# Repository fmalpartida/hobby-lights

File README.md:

# hobby-lights
Small light sequencer for hobby projects.

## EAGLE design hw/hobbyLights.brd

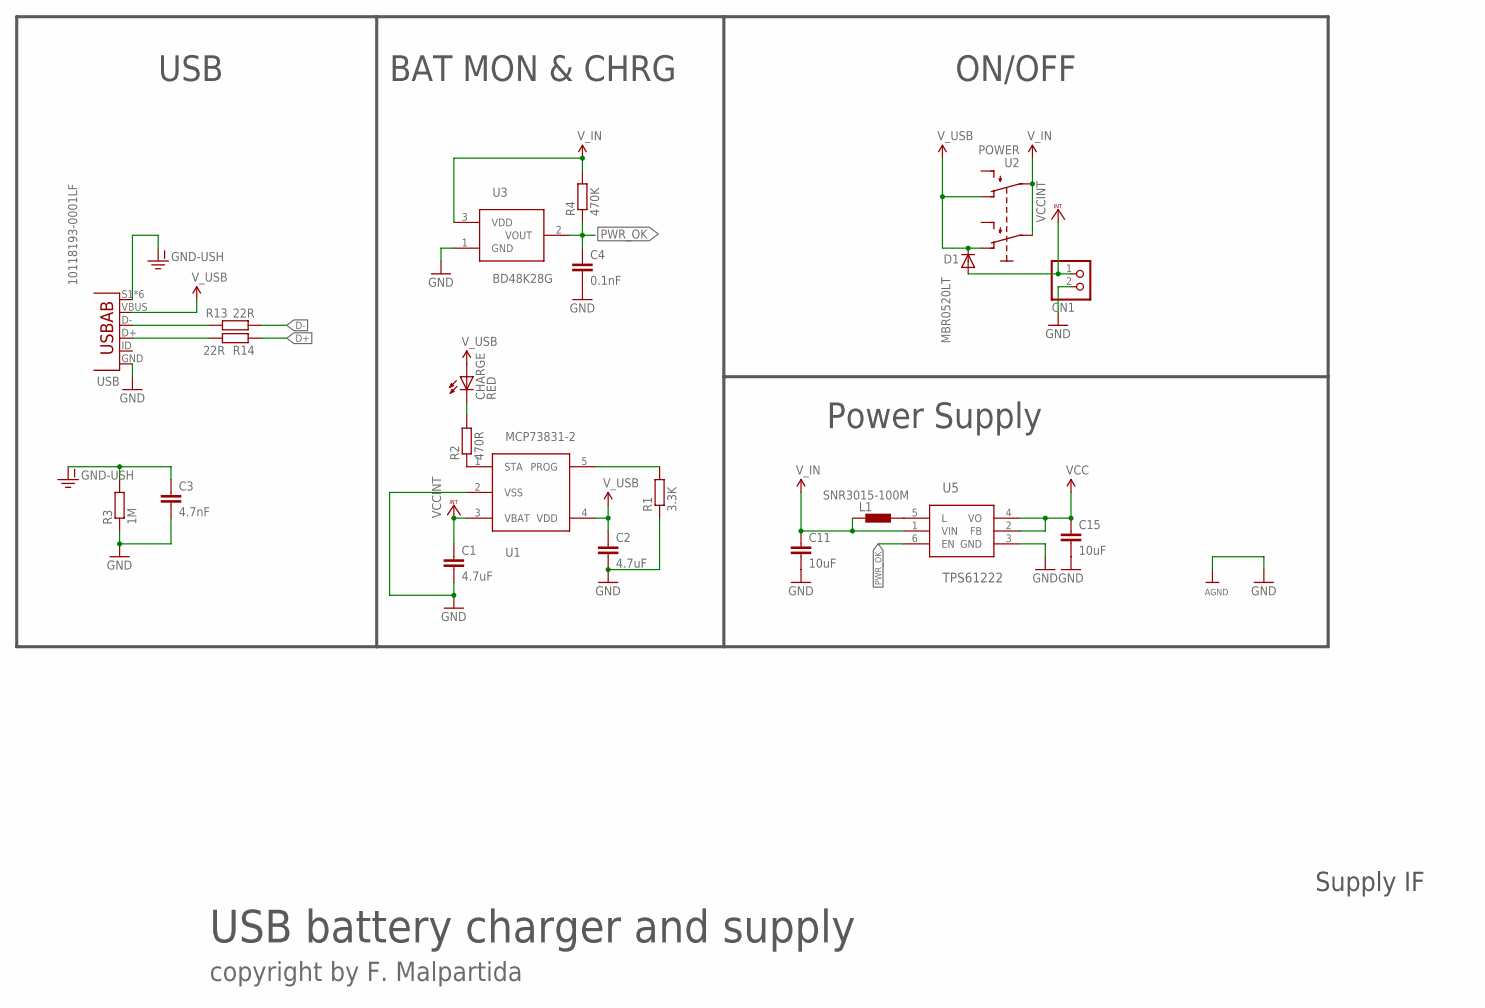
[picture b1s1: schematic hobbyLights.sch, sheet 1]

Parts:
C1, C2: 4.7uF; C0805
C3: 4.7nF; C0603
C4: 0.1nF; C0603
C11, C15: 10uF; C0805
CHARGE: RED; CHIPLED_0805
CN1: JST_2PIN-THM-RA; JST-PH-2-THM-RA
D1: MBR0520LT; SOD123
L1: SNR3015-100M; SRN3015
R1: 3.3K; R0603
R2: 470R; R0603
R3: 1M; R0603
R4: 470K; R0603
R13, R14: 22R; R0603
U1: MCP73831-2; SOT23-5
U2: POWER; SWITCH-JS202011
U3: BD48K28G; SSOP3
U5: TPS61222; DCK
USB: 10118193-0001LF; USB_MICRO_B

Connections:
D+: R14.1; also elsewhere on the board
D-: R13.1; also elsewhere on the board
GND: C1.2, C2.2, C3.2, C4.2, C11.2, C15.2, CN1.2 (1), R1.1, R3.1, U1.2 (VSS), U3.1 (GND), U5.3 (GND), USB.GND; also elsewhere on the board
GND-ISO: C3.1, R3.2, USB.S1 (SHIELD), USB.S2 (SHIELD), USB.S3 (SHIELD), USB.S4 (SHIELD), USB.S5 (SHIELD), USB.S6 (SHIELD)
unnamed: R1.2, U1.5 (PROG)
unnamed: R2.1, U1.1 (STA)
unnamed: CHARGE.C, R2.2
unnamed: R13.2, USB.D-
unnamed: R14.2, USB.D+
unnamed: L1.2, U5.5 (L)
PWR_OK: C4.1, R4.1, U3.2 (VOUT), U5.6 (EN)
VCC: C15.1, U5.2 (FB), U5.4 (VO); also elsewhere on the board
VCCINT: C1.1, CN1.1 (2), D1.A, U1.3 (VBAT)
V_BATT: C11.1, L1.1, R4.2, U2.P2, U2.P5 (P1), U3.3 (VDD), U5.1 (VIN); also elsewhere on the board
V_USB: C2.1, CHARGE.A, D1.C, U1.4 (VDD), U2.P1 (O), U2.P4 (O1), USB.VBUS

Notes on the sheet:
USB
BAT MON & CHRG
Power Supply
ON/OFF
USB battery charger and supply
Supply IF
copyright by F. Malpartida

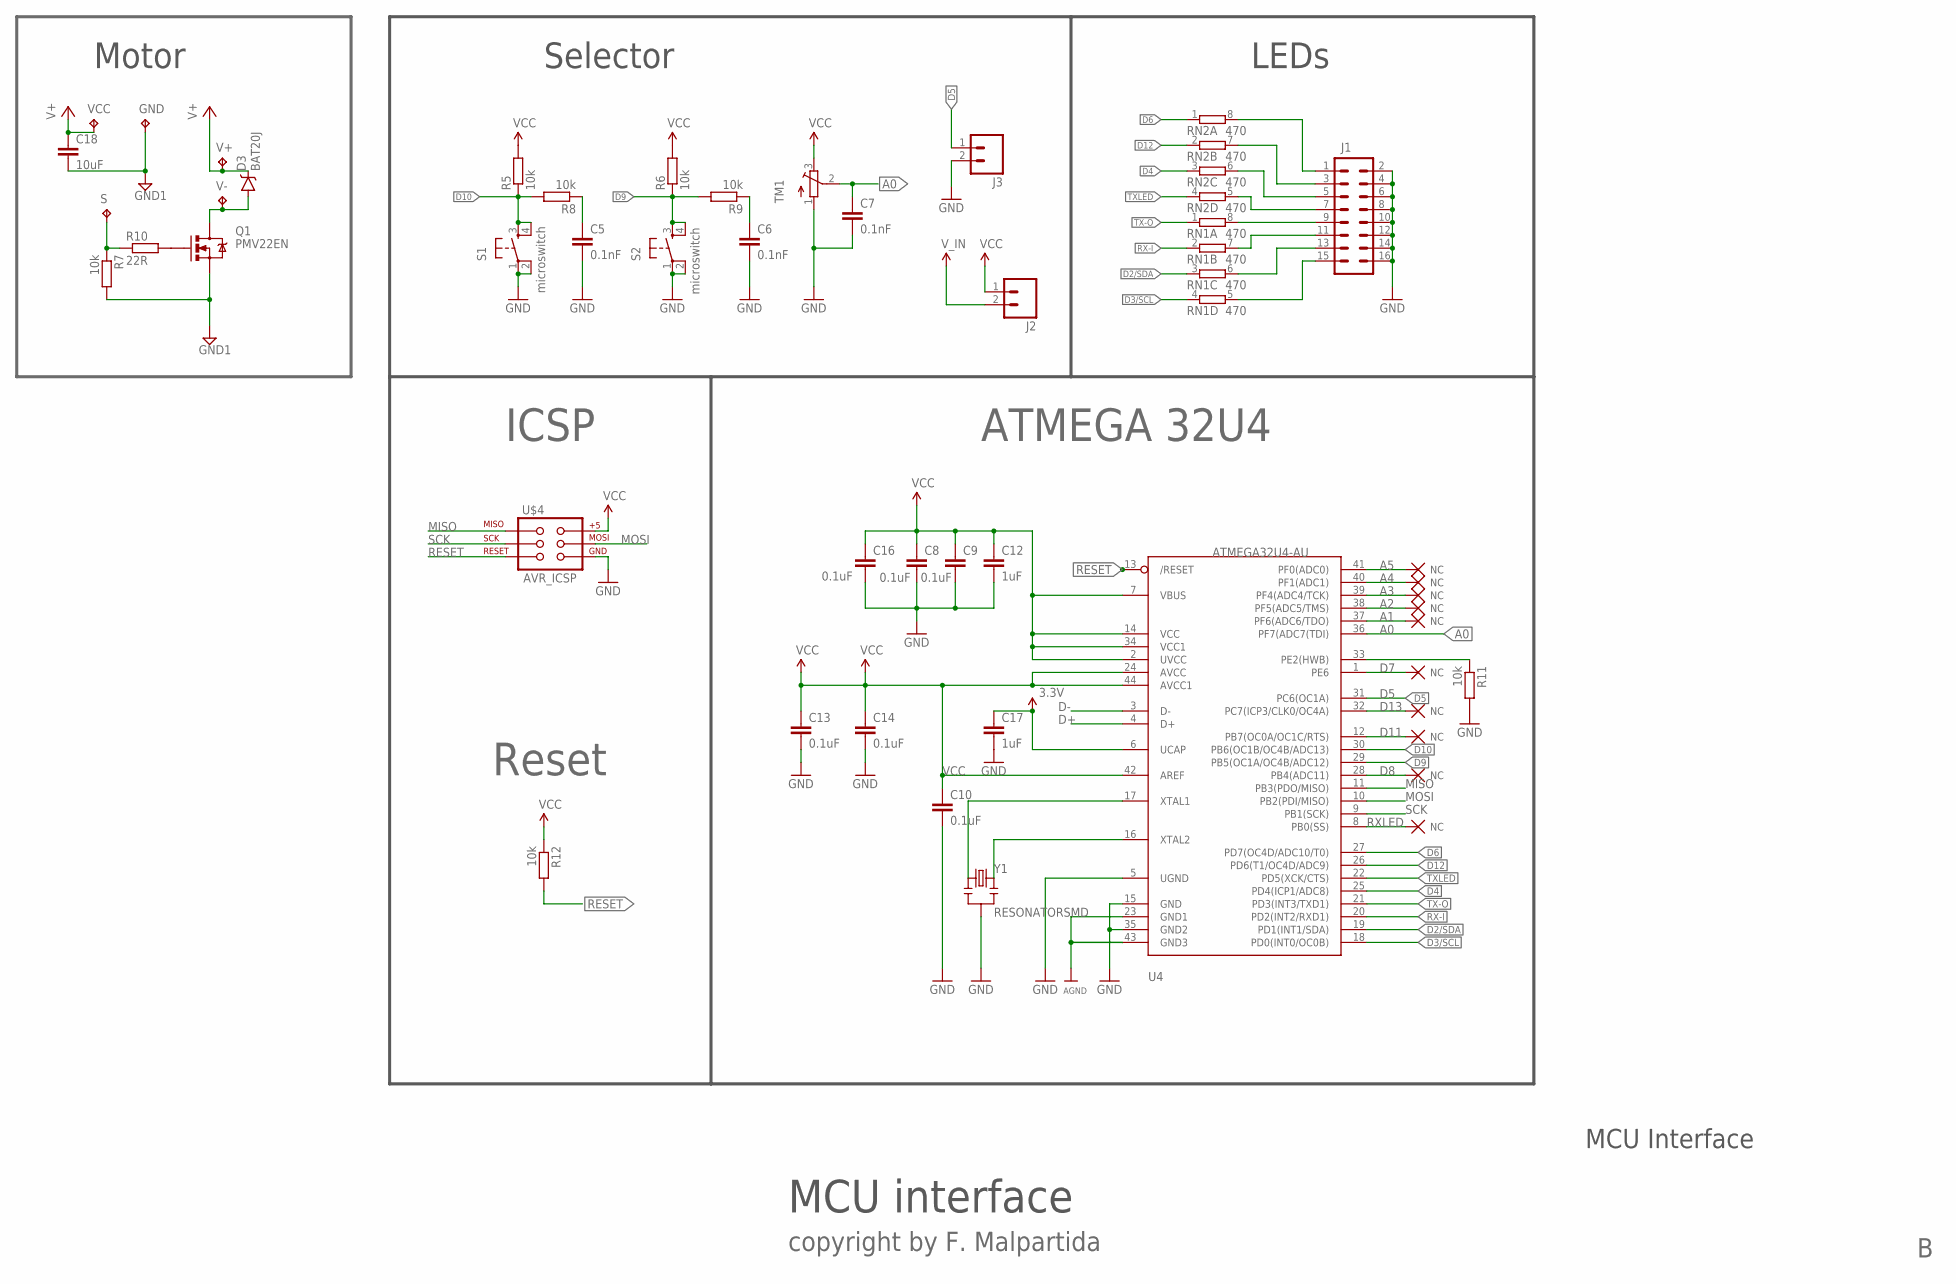
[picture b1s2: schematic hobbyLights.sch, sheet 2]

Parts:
C5, C6, C7: 0.1nF; C0603
C8, C9, C10, C13, C14, C16: 0.1uF; C0603
C12, C17: 1uF; C0603
C18: 10uF; C0805
D3: BAT20J; SOD-323
GND: TPTP20SQ; TP20SQ
J1: M08X2; 2X8
J2, J3: M02PTH; 1X02
Q1: PMV22EN; SOT23-3
R5, R6, R7, R8, R9, R11, R12: 10k; R0603
R10: 22R; R0603
RN1, RN2: 470; EXBS8V
S: TPTP20SQ; TP20SQ
S1, S2: microswitch; SPARKFUN_TACTILE_SWITCH_SMD
TM1: TRIMPOTTC33X; TC33X
U4: ATMEGA32U4-AU; ADAFRUIT_TQFP44
U$4: AVR_ICSP; ICSP_SMD
V+: TPTP20SQ; TP20SQ
V-: TPTP20SQ; TP20SQ
VCC: TPTP20SQ; TP20SQ
Y1: RESONATORSMD; RESONATOR-SMD

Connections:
3.3V: C17.1, U4.6 (UCAP)
A0: C7.1, TM1.2 (S), U4.36 (PF7(ADC7(TDI))
A1: U4.37 (PF6(ADC6/TDO))
A2: U4.38 (PF5(ADC5/TMS))
A3: U4.39 (PF4(ADC4/TCK))
A4: U4.40 (PF1(ADC1))
A5: U4.41 (PF0(ADC0))
D2/SDA: RN1.3 (1), U4.19 (PD1(INT1/SDA))
D3/SCL: RN1.4 (1), U4.18 (PD0(INT0/OC0B))
D4: RN2.3 (1), U4.25 (PD4(ICP1/ADC8))
D5: J3.1, U4.31 (PC6(OC1A))
D6: RN2.1, U4.27 (PD7(OC4D/ADC10/T0))
D7: U4.1 (PE6)
D8: U4.28 (PB4(ADC11))
D9: R6.1, R9.2, S2.3, S2.4, U4.29 (PB5(OC1A/OC4B/ADC12))
D10: R5.1, R8.2, S1.3, S1.4, U4.30 (PB6(OC1B/OC4B/ADC13))
D11: U4.12 (PB7(OC0A/OC1C/RTS))
D12: RN2.2 (1), U4.26 (PD6(T1/OC4D/ADC9))
D13: U4.32 (PC7(ICP3/CLK0/OC4A))
D+: U4.4 (D+); also elsewhere on the board
D-: U4.3 (D-); also elsewhere on the board
GND: C5.2, C6.2, C7.2, C8.2, C9.2, C10.2, C12.2, C13.2, C14.2, C16.2, C17.2, J1.2, J1.4, J1.6, J1.8, J1.10, J1.12, J1.14, J1.16, J3.2, R11.2, S1.1, S1.2, S2.1, S2.2, TM1.1 (A), U4.5 (UGND), U4.15 (GND), U4.23 (GND1), U4.35 (GND2), U4.43 (GND3), U$4.GND, Y1.2; also elsewhere on the board
GND1: C18.2, GND.TP, Q1.2 (S), R7.2
MISO: U4.11 (PB3(PDO/MISO)), U$4.MISO
MOSI: U4.10 (PB2(PDI/MISO)), U$4.MOSI
unnamed: Q1.1 (G), R10.2
unnamed: C5.1, R8.1
unnamed: U4.16 (XTAL2), Y1.3
unnamed: U4.17 (XTAL1), Y1.1
unnamed: R7.1, R10.1, S.TP
unnamed: C6.1, R9.1
unnamed: D3.A, Q1.3 (D), V-.TP
unnamed: R11.1, U4.33 (PE2(HWB))
unnamed: J1.15, RN1.5 (2)
unnamed: J1.13, RN1.6 (2)
unnamed: J1.11, RN1.7 (2)
unnamed: J1.9, RN1.8 (2)
unnamed: J1.1, RN2.8 (2)
unnamed: J1.3, RN2.7 (2)
unnamed: J1.5, RN2.6 (2)
unnamed: J1.7, RN2.5 (2)
RESET: R12.2, U4.13 (/RESET), U$4.RESET
RX-I: RN1.2 (1), U4.20 (PD2(INT2/RXD1))
RXLED: U4.8 (PB0(SS))
SCK: U4.9 (PB1(SCK)), U$4.SCK
TX-O: RN1.1, U4.21 (PD3(INT3/TXD1))
TXLED: RN2.4 (1), U4.22 (PD5(XCK/CTS))
V+: C18.1, D3.C, V+.TP, VCC.TP
VCC: C8.1, C9.1, C10.1, C12.1, C13.1, C14.1, C16.1, J2.1, R5.2, R6.2, R12.1, TM1.3 (E), U4.2 (UVCC), U4.7 (VBUS), U4.14 (VCC), U4.24 (AVCC), U4.34 (VCC1), U4.42 (AREF), U4.44 (AVCC1), U$4.5V (+5V); also elsewhere on the board
V_BATT: J2.2; also elsewhere on the board

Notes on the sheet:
ATMEGA 32U4
Reset
ICSP
Selector
LEDs
MCU interface
MCU Interface
copyright by F. Malpartida
Motor

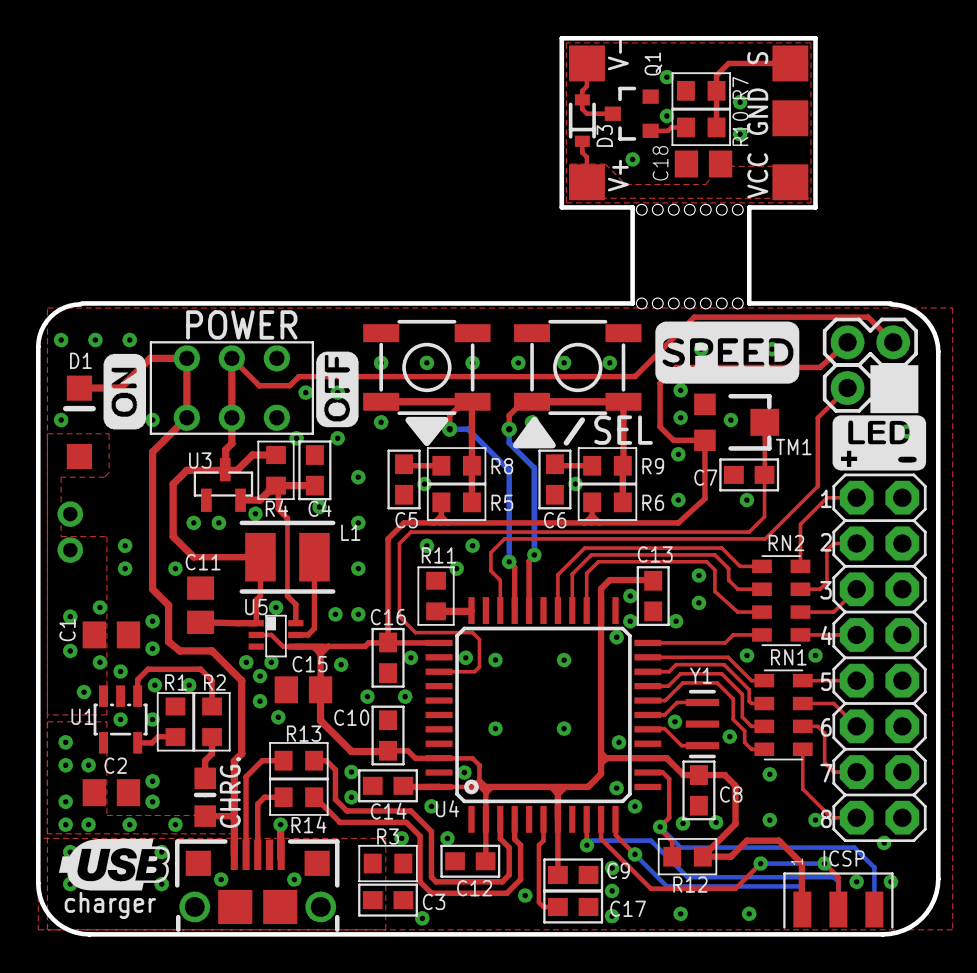
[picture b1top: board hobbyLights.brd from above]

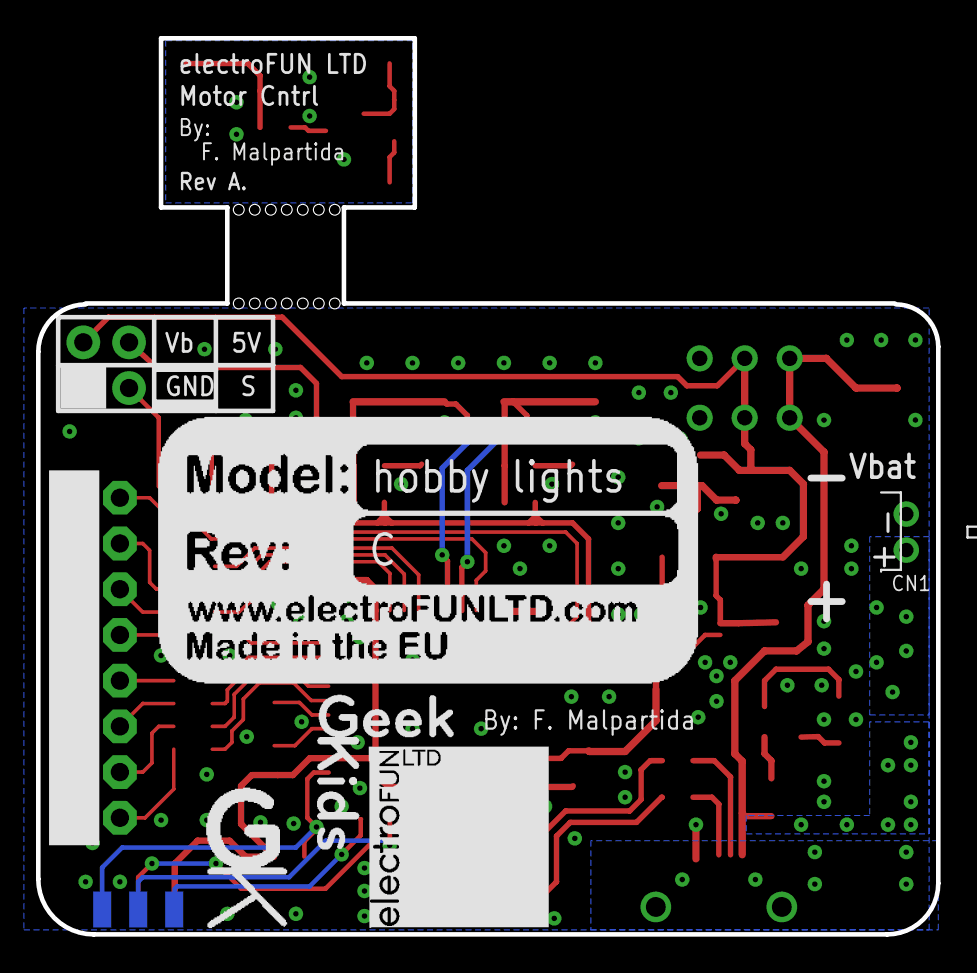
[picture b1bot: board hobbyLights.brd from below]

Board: 2 copper layers, 50.0 x 49.8 mm, 68 parts (5 on the bottom side), 50 nets.

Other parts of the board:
U$1: LED_SILK
U$2: ON
U$3: OFF
U$5: ELECTROFUN_10X10
U$7: GEEKKIDS_S
U$11: GEEKKIDS_LOGO_S
U$17: SPEED
U$23: USB_LOGO
U$24: BOARD_REF_M

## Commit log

2016-03-23 First project version.
2016-03-23 Added EEPROM support and pulled in EEPROM library for compiling.
2016-03-23 Moved storage support to program. Cleaned program code to hide internals.
2016-03-23 Minor code cleaning.
2016-03-26 Reworked entire project: - included references to sequencing tables as opposed to sequencer objects. - included additional support for managing programs. - added serial interface support to select: p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
2016-03-26 Added additional programs and sequences.
2016-04-03 Added HW to the project.
2016-04-03 Ignoring some HW files.
2016-04-03 Updated diodes and added frames.
2016-04-03 Ignoring backup files.
2016-04-03 Removed side boards.
2016-04-09 Added daughter boards for high side switching.
2016-04-10 Minor reviews on the PCB
2016-04-10 Added interrupt management for unattended sequencing. Added new sequence for fast blink.
2016-04-16 Adding button support
2016-04-16 Added capability to load program or not from memory. Avoid writing back to EEPROM the loaded program during initialisation. Added local echo and changed f command by s.
2016-04-17 Added controller, updated buttons and associated methods. Renamed class variables for usage.
2016-04-17 First version completed.
2016-04-29 Updated PCB removing daughter motor boards.
2016-05-01 Initial program configuration.
2016-05-01 Updated buttons so that they don't use new by composition in the controller. Refactored button configuration initialisation.
2016-05-01 Updated schematic for Rev B.
2016-05-01 Updates for production - Rev B
2016-05-15 Fixed button direction to match serigraphy and added reset program action on double click on the select button.
2016-05-19 Added alternating lights on all channels.
2016-05-20 Organised descriptors.
2016-05-28 Minor modifications and upgrade to Eagle 7.6.0
2016-05-29 Added cylon raider light sequence: chaser + guns + engines
2016-05-30 Added count up and down, KIT, cylon raider inverse light effect.
2016-06-04 HW: - updated resistor values to increase LED brightness. - updated resistor values to increase charge current. SW: - added new blink program - added new serial line command i.
2016-06-04 Cleaned up code removing unused variables.
2016-06-05 Updated printing information and moved it to the program class.
2016-06-05 Rev C board preparation: changed select button by trim pot, changed battery connector for JST PH RA.
2016-06-05 Updated to use JST PH connector. Updates to serigraphy.
2016-06-05 Added block diagram.
2016-06-08 Minor updates.
2016-06-19 Made adjustments to the board.
2016-07-02 Added motor support.
2016-07-03 Minor updates and silk screen improvements.
2016-07-03 Revision for PCB fab-house.
2016-07-08 Added: - cylon raider 2 (only engines) - US crossing lights - UK crossing lights
    Minor board updates.

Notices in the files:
parts and their libraries:
SparkFun-Connectors: Licensing: Creative Commons ShareAlike 4.0 International - https://creativecommons.org/licenses/by-sa/4.0
